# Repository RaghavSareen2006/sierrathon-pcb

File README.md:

# Sierrathon PCB Design – Pocket Lab

KiCad 10 project for the Sierrathon PCB design hackathon.
Pocket Lab: a keyring-sized USB logic analyzer / voltmeter for engineering students.
Specs, BOM and scoring live in `Resources/`.

## Board outline (done)
- Rounded stick, 75 x 27 mm, 3 mm corners. USB-C on BOTH ends:
  J1 (left, silkscreen "PC") goes to the laptop, J2 (right, silkscreen "PROBE") goes to the circuit under test.
- M4 holes sit right behind each USB-C so the screws take plug-in force:
  MH1/MH3 at (13, 6)/(13, 21), MH2/MH4 at (62, 6)/(62, 21). MH4 doubles as the keyring hole.
  Coordinates are mm from the board's top-left (grid origin is set there).
- Blue drawings on `User.Comments` are placement guides only (J1, J2, RP2040 zone, LED zone,
  R20-R25 zone, hole circles). Delete them once parts are placed.

## Probe port J2 (judges approved adding a USB-C) - ON THE BOARD
J2 is the same USB-C part as J1 (Same Sky UJ20-C-H-G-SMT-TR, SeoHan's CUI_UJ20 footprint), at the right
end of the board, rotated 180 deg from J1. Each signal goes through a 1 kOhm series resistor (R20-R25,
same part as R7/R8) placed right behind J2.

| J2 pins | via | Net | RP2040 |
|---|---|---|---|
| A6 + B6 (D+, tied) | R20 | CH0 | GPIO9 (pin 12) |
| A7 + B7 (D-, tied) | R21 | CH1 | GPIO10 (pin 13) |
| A8 (SBU1) | R22 | CH2 | GPIO11 (pin 14) |
| B8 (SBU2) | R23 | CH3 | GPIO12 (pin 15) |
| A5 (CC1) | R24 | A0 | GPIO26 / ADC0 (pin 38) |
| B5 (CC2) | R25 | A1 | GPIO28 / ADC2 (pin 40) |
| GND pins + shell | | GND | |
| VBUS pins | | not connected (a charger/laptop plugged in here can't push 5 V in) | |

CH0-CH3 are 4 consecutive GPIOs (needed for the PIO logic-analyzer). GPIO0-3 / GPIO27 were the first
plan but there is no room to escape 4 vias under those 0.4 mm-pitch pins, so the channels moved to
GPIO9-12 and A1 to GPIO28 (both still analog-capable / consecutive). Drawn on the main sheet (top right)
with local labels; GPIO0-3 and GPIO27 keep their no-connect flags.

## Team rules for working in this repo
- KiCad files don't merge well. **Only one person edits a given file at a time**
  (`.kicad_sch` = schematic, `.kicad_pcb` = board). Say so in the team chat before you start.
- Before you open KiCad: `git pull`. When you're done: save, close KiCad, then commit and push.
- Never commit while the file is open and unsaved.

## Design rules (already set up – don't change without telling the team)
- 4 layers, 62 mil, 1 oz copper, FR-370HR, green mask / white silk (Board Setup > Physical Stackup).
- Constraints page floors are 4 mil clearance / 5 mil track **on purpose**: they must equal the
  90 Ω USB pair geometry (5 mil trace, 4 mil gap). Everything else is held to 6 mil by net
  classes and by `Sierrathon-PCB Design.kicad_dru` (Board Setup > Custom Rules).
- Net classes: `USB_90R` (USB_P/N, USBR_P/N, D_P/D_N – use the diff-pair router, key `6`),
  `Power` (VBUS, +3.3V, +1.1V, GND – 15 mil), `Default` (8 mil).
- Net names in the schematic must match the PDF exactly or nets won't land in the right class.

## Routing (done - DRC: 0 violations, 0 unconnected, schematic parity clean)
- USB (D_P/D_N, USB_P/USB_N, USBR_P/USBR_N) hand-routed and locked: 5 mil traces, 4 mil gap where
  the pair runs in parallel. USBR_N hops under USBR_P on B.Cu (one via pair) because the ESD chip's
  channel order is the reverse of the RP2040's USB_DM/USB_DP pin order.
- `diff_pair_uncoupled` limit is 7 mm (was 3 mm): each pair has to split around U4, R5/R6 and the swap;
  fine for full-speed USB (12 Mb/s).
- Remaining signals auto-routed with Freerouting (F.Cu/B.Cu only); In1.Cu = GND plane, In2.Cu = +3.3V
  plane (layer type "power", 8 mil plane clearance). GND/+3.3V pads drop to the planes through vias;
  RP2040 exposed pad has 6 thermal vias.
- Y1 uses an exact Abracon ABM8 land pattern (Libraries/Sierrathon.pretty, datasheet in Libraries/datasheets).

## Current status (3:05 PM) - SeoHan's schematic and footprints
- Project schematic = SeoHan's `finalschematic.kicad_sch` (only change: internal project name pointed at this project).
- J1, SW1, SW2, SW3, U3, Y1 use SeoHan's footprints (CUI_UJ20-C-H-G-SMT-TR, SON4_PTS526 SM15 SMTR2 LFS_CNK,
  D6R90_CNK, SOIC127P790X216-8N, XTAL_ABM8-272-T3), aligned pad-for-pad to the routed board. Small DFM edits:
  J1 signal-pin mask margin 0.102 -> 0.04 mm (keeps a mask web at 0.85 mm pitch), J1 silk past the board edge
  removed, duplicate "*" silk text on the PTS526 removed, U3 pin-1 silk dot that sat on copper removed.
- Rules: min annular ring 0.127 -> 0.12 mm (J1 pads have a 0.125 mm ring); USB_90R class + a 4 mil in-pair rule
  also cover the auto-named Net-(U1-USB_DP) / Net-(U1-USB_DM) nets.
- DRC --severity-all --schematic-parity: 0 violations, 0 unconnected, 0 footprint errors.
- Known schematic items left as-is for now: USBR_P/USBR_N and Led5 net names, BOM values on J1/MH1-4/SW3/U2,
  most parts have no MPN/Manufacturer fields, ERC warnings from downloaded symbols' pin types.
- My earlier footprints (SW_CK_*, USB_C_Receptacle_SameSky_*, Crystal_SMD_Abracon_ABM8-*) stay in the library, unused.

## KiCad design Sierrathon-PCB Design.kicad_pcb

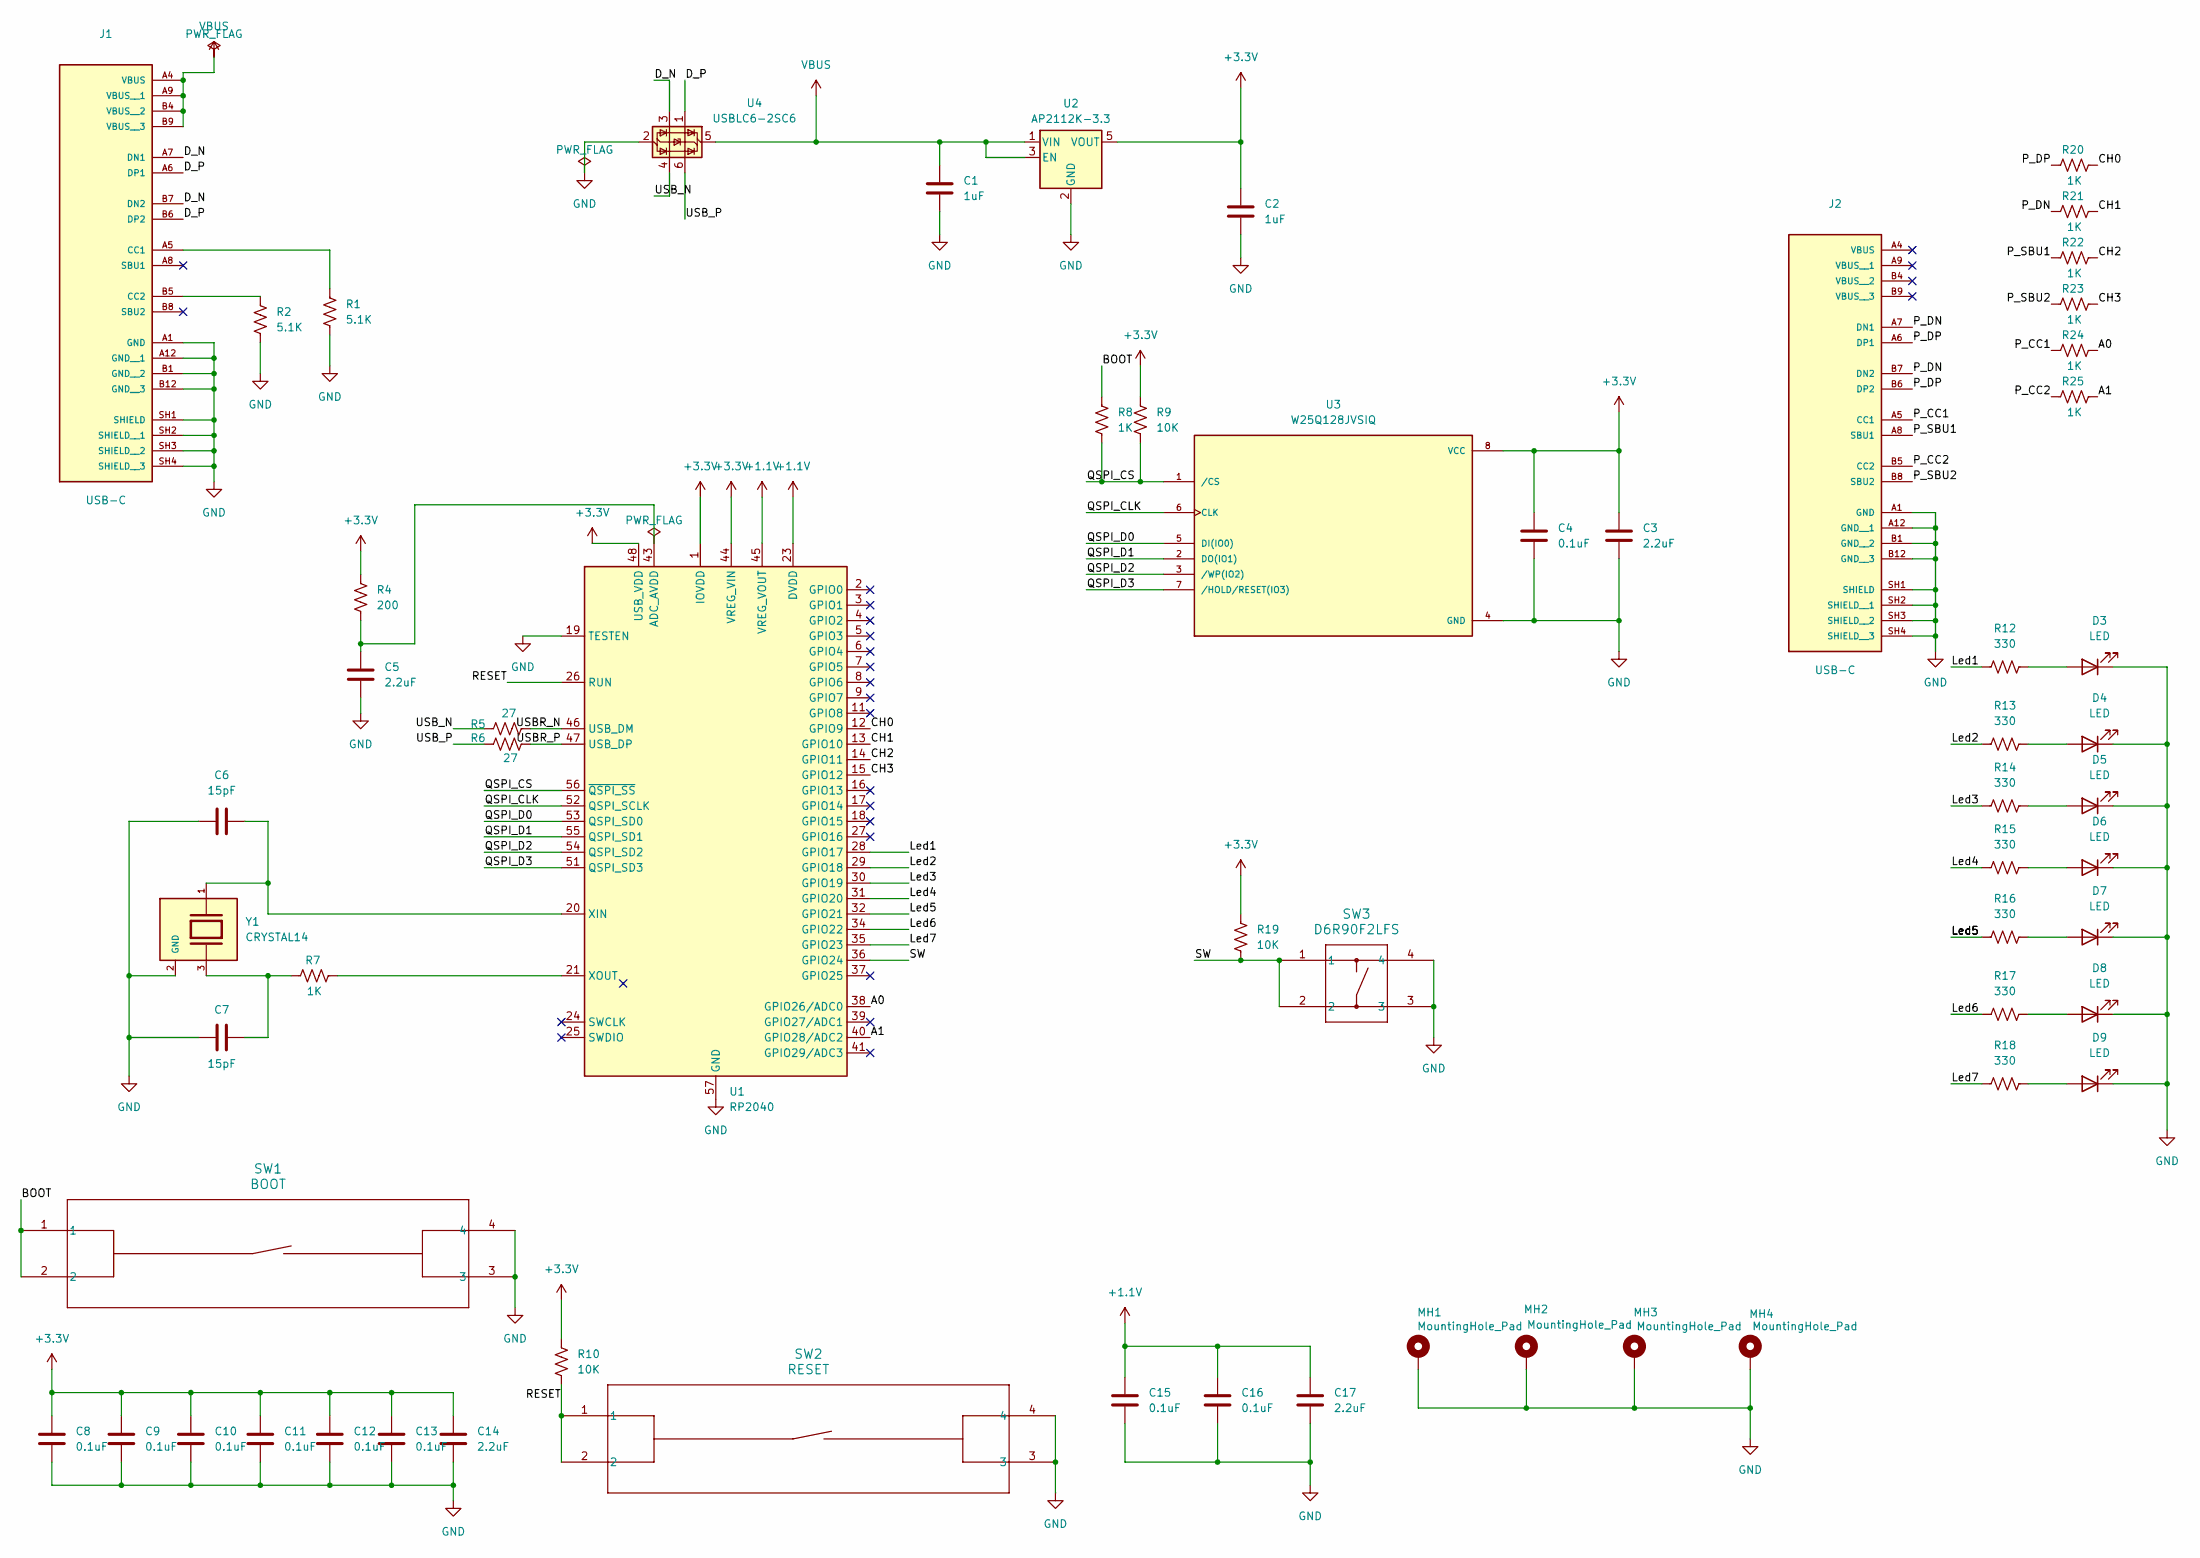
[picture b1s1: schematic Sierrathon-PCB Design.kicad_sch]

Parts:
C1, C2: 1uF; C_0603_1608Metric; MPN GCM188R71C105KA64D
C3, C5, C14, C17: 2.2uF; C_0805_2012Metric; MPN GCM21BR71C225KA64L
C4, C8, C9, C10, C11, C12, C13, C15, C16: 0.1uF; C_0402_1005Metric; MPN GCM155R71C104KA55D
C6, C7: 15pF; C_0402_1005Metric; MPN GCM1555C1H150JA16D
D3, D4, D5, D6, D7, D8, D9: LED; LED_0603_1608Metric; MPN QBLP601-R5
J1, J2: USB-C; CUI_UJ20-C-H-G-SMT-TR; MPN UJ20-C-H-G-SMT-TR
MH1, MH2, MH3, MH4: MountingHole_Pad; MountingHole_4.3mm_M4_Pad
R1, R2: 5.1K; R_0402_1005Metric; MPN RC0402JR-075K1L
R4: 200; R_0603_1608Metric; MPN RC0603JR-07200RL
R5, R6: 27; R_0402_1005Metric; MPN RC0402FR-0727RL
R7, R8, R20, R21, R22, R23, R24, R25: 1K; R_0402_1005Metric; MPN RC0402FR-071KL
R9, R10, R19: 10K; R_0402_1005Metric; MPN RC0402JR-0710KL
R12, R13, R14, R15, R16, R17, R18: 330; R_0402_1005Metric; MPN AF0402JR-07330RL
SW1: BOOT; SON4_PTS526 SM15 SMTR2 LFS_CNK; MPN PTS526SM15SMTR2 LFS
SW2: RESET; SON4_PTS526 SM15 SMTR2 LFS_CNK; MPN PTS526SM15SMTR2 LFS
SW3: D6R90F2LFS; D6R90_CNK; MPN D6R90 F2 LFS
U1: RP2040; QFN-56-1EP_7x7mm_P0.4mm_EP3.2x3.2mm; MPN SC0914(13)
U2: AP2112K-3.3; SOT-23-5; MPN AP2112K-3.3TRG1
U3: W25Q128JVSIQ; SOIC127P790X216-8N; MPN W25Q128JVSIQ TR
U4: USBLC6-2SC6; SOT-23-6; MPN USBLC6-2SC6
Y1: CRYSTAL14; XTAL_ABM8-272-T3; MPN ABM8-272-T3

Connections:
+1.1V: C15.2, C16.2, C17.2, U1.23 (DVDD), U1.45 (VREG_VOUT), U1.50 (DVDD)
+3.3V: C2.1, C3.1, C4.1, C8.2, C9.2, C10.2, C11.2, C12.2, C13.2, C14.2, R4.1, R9.2, R10.2, R19.1, U1.1 (IOVDD), U1.10 (IOVDD), U1.22 (IOVDD), U1.33 (IOVDD), U1.42 (IOVDD), U1.44 (VREG_VIN), U1.48 (USB_VDD), U1.49 (IOVDD), U2.5 (VOUT), U3.8 (VCC)
/A0: R24.2, U1.38 (GPIO26/ADC0)
/A1: R25.2, U1.40 (GPIO28/ADC2)
/BOOT: R8.2, SW1.1, SW1.2
/CH0: R20.2, U1.12 (GPIO9)
/CH1: R21.2, U1.13 (GPIO10)
/CH2: R22.2, U1.14 (GPIO11)
/CH3: R23.2, U1.15 (GPIO12)
/D_N: J1.A7 (DN1), J1.B7 (DN2), U4.3 (I/O2)
/D_P: J1.A6 (DP1), J1.B6 (DP2), U4.1 (I/O1)
/Led1: R12.2, U1.28 (GPIO17)
/Led2: R13.2, U1.29 (GPIO18)
/Led3: R14.2, U1.30 (GPIO19)
/Led4: R15.2, U1.31 (GPIO20)
/Led5: R16.2, U1.32 (GPIO21)
/Led6: R17.2, U1.34 (GPIO22)
/Led7: R18.2, U1.35 (GPIO23)
/P_CC1: J2.A5 (CC1), R24.1
/P_CC2: J2.B5 (CC2), R25.1
/P_DN: J2.A7 (DN1), J2.B7 (DN2), R21.1
/P_DP: J2.A6 (DP1), J2.B6 (DP2), R20.1
/P_SBU1: J2.A8 (SBU1), R22.1
/P_SBU2: J2.B8 (SBU2), R23.1
/QSPI_CLK: U1.52 (QSPI_SCLK), U3.6 (CLK)
/QSPI_CS: R8.1, R9.1, U1.56 (~QSPI_SS), U3.1 (/CS)
/QSPI_D0: U1.53 (QSPI_SD0), U3.5 (DI(IO0))
/QSPI_D1: U1.55 (QSPI_SD1), U3.2 (DO(IO1))
/QSPI_D2: U1.54 (QSPI_SD2), U3.3 (/WP(IO2))
/QSPI_D3: U1.51 (QSPI_SD3), U3.7 (/HOLD/RESET(IO3))
/RESET: R10.1, SW2.1, SW2.2, U1.26 (RUN)
/SW: R19.2, SW3.1, SW3.2, U1.36 (GPIO24)
/USBR_N: R5.2, U1.46 (USB_DM)
/USBR_P: R6.2, U1.47 (USB_DP)
/USB_N: R5.1, U4.4 (I/O2)
/USB_P: R6.1, U4.6 (I/O1)
GND: C1.2, C2.2, C3.2, C4.2, C5.2, C6.1, C7.2, C8.1, C9.1, C10.1, C11.1, C12.1, C13.1, C14.1, C15.1, C16.1, C17.1, D3.1 (K), D4.1 (K), D5.1 (K), D6.1 (K), D7.1 (K), D8.1 (K), D9.1 (K), J1.A1 (GND), J1.A12 (GND__1), J1.B1 (GND__2), J1.B12 (GND__3), J1.SH1 (SHIELD), J1.SH2 (SHIELD__1), J1.SH3 (SHIELD__2), J1.SH4 (SHIELD__3), J2.A1 (GND), J2.A12 (GND__1), J2.B1 (GND__2), J2.B12 (GND__3), J2.SH1 (SHIELD), J2.SH2 (SHIELD__1), J2.SH3 (SHIELD__2), J2.SH4 (SHIELD__3), MH1.1 (1_1), MH2.1 (1_1), MH3.1 (1_1), MH4.1 (1_1), R1.2, R2.2, SW1.3, SW1.4, SW2.3, SW2.4, SW3.3, SW3.4, U1.19 (TESTEN), U1.57 (GND), U2.2 (GND), U3.4 (GND), U4.2 (GND), Y1.2 (GND), Y1.4 (GND)
unnamed: C7.1, R7.1, Y1.3
unnamed: D3.2 (A), R12.1
unnamed: D4.2 (A), R13.1
unnamed: D5.2 (A), R14.1
unnamed: D6.2 (A), R15.1
unnamed: D7.2 (A), R16.1
unnamed: D8.2 (A), R17.1
unnamed: D9.2 (A), R18.1
unnamed: J1.A5 (CC1), R1.1
unnamed: J1.B5 (CC2), R2.1
unnamed: C5.1, R4.2, U1.43 (ADC_AVDD)
unnamed: C6.2, U1.20 (XIN), Y1.1
unnamed: R7.2, U1.21 (XOUT)
VBUS: C1.1, J1.A4 (VBUS), J1.A9 (VBUS__1), J1.B4 (VBUS__2), J1.B9 (VBUS__3), U2.1 (VIN), U2.3 (EN), U4.5 (VBUS)

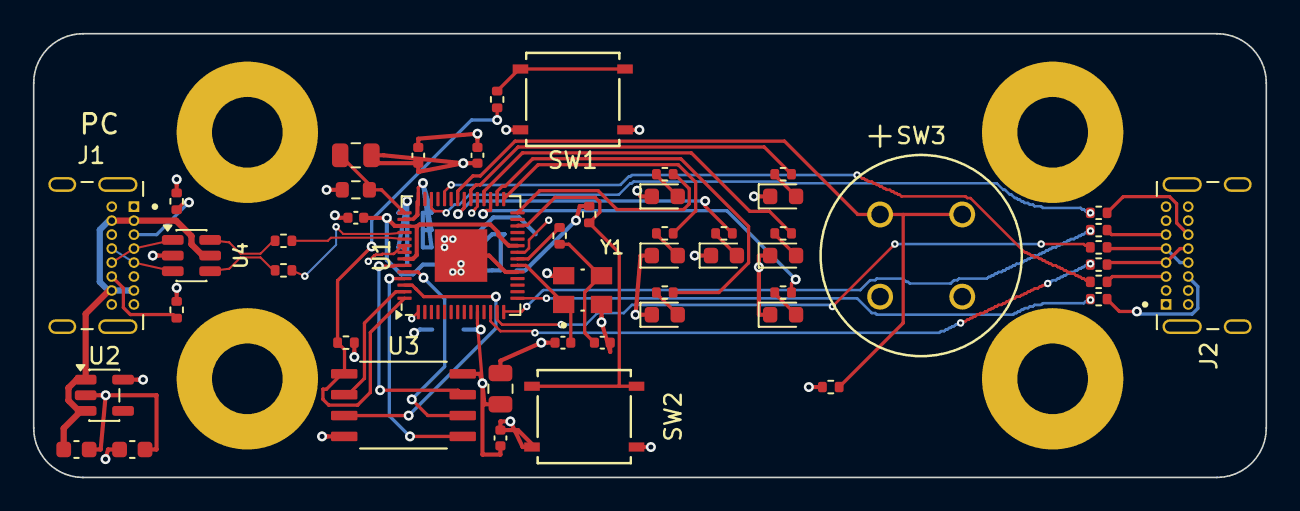
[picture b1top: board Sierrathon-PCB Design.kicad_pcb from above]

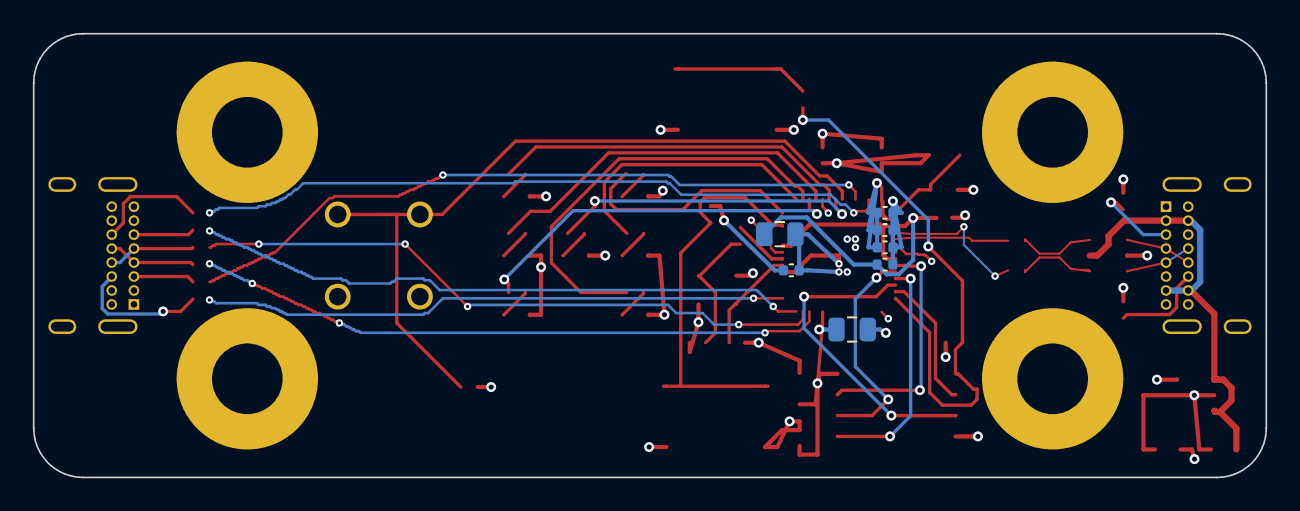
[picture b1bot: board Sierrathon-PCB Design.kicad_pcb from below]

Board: 4 copper layers, 75.0 x 27.0 mm, 61 parts (7 on the bottom side), 51 nets.

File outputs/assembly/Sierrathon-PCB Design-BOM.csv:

"Reference","Value","Footprint","Qty","MPN","Manufacturer","Description","DNP"
"C1,C2","1uF","Capacitor_SMD:C_0603_1608Metric","2","GCM188R71C105KA64D","Murata Electronics","Unpolarized capacitor",""
"C3,C5,C14,C17","2.2uF","Capacitor_SMD:C_0805_2012Metric","4","GCM21BR71C225KA64L","Murata Electronics","Unpolarized capacitor",""
"C4,C8,C9,C10,C11,C12,C13,C15,C16","0.1uF","Capacitor_SMD:C_0402_1005Metric","9","GCM155R71C104KA55D","Murata Electronics","Unpolarized capacitor",""
"C6,C7","15pF","Capacitor_SMD:C_0402_1005Metric","2","GCM1555C1H150JA16D","Murata Electronics","Unpolarized capacitor",""
"D3,D4,D5,D6,D7,D8,D9","LED","LED_SMD:LED_0603_1608Metric","7","QBLP601-R5","QT Brightek (QTB)","Light emitting diode",""
"J1,J2","USB-C","Sierrathon:CUI_UJ20-C-H-G-SMT-TR","2","UJ20-C-H-G-SMT-TR","Same Sky (Formerly CUI Devices)","Type C, USB 2.0, 480 Mbps, 20 Vdc, 5 A, Right Angle, Gold Flash, Surface Mount, Black Insulator, USB Receptacle",""
"R1,R2","5.1K","Resistor_SMD:R_0402_1005Metric","2","RC0402JR-075K1L","YAGEO","Resistor, US symbol",""
"R4","200","Resistor_SMD:R_0603_1608Metric","1","RC0603JR-07200RL","YAGEO","Resistor, US symbol",""
"R5,R6","27","Resistor_SMD:R_0402_1005Metric","2","RC0402FR-0727RL","YAGEO","Resistor, US symbol",""
"R7,R8,R20,R21,R22,R23,R24,R25","1K","Resistor_SMD:R_0402_1005Metric","8","RC0402FR-071KL","YAGEO","Resistor, US symbol",""
"R9,R10,R19","10K","Resistor_SMD:R_0402_1005Metric","3","RC0402JR-0710KL","YAGEO","Resistor, US symbol",""
"R12,R13,R14,R15,R16,R17,R18","330","Resistor_SMD:R_0402_1005Metric","7","AF0402JR-07330RL","YAGEO","Resistor, US symbol",""
"SW1","BOOT","Sierrathon:SON4_PTS526 SM15 SMTR2 LFS_CNK","1","PTS526SM15SMTR2 LFS","C&K","",""
"SW2","RESET","Sierrathon:SON4_PTS526 SM15 SMTR2 LFS_CNK","1","PTS526SM15SMTR2 LFS","C&K","",""
"SW3","D6R90F2LFS","Sierrathon:D6R90_CNK","1","D6R90 F2 LFS","C&K","",""
"U1","RP2040","Package_DFN_QFN:QFN-56-1EP_7x7mm_P0.4mm_EP3.2x3.2mm","1","SC0914(13)","Raspberry Pi","A microcontroller by Raspberry Pi, Dual ARM Cortex-M0+, 133MHz, no flash, 264KB SRAM, 8 PIO state machines, VQFN-56",""
"U2","AP2112K-3.3","Package_TO_SOT_SMD:SOT-23-5","1","AP2112K-3.3TRG1","Diodes Incorporated","600mA low dropout linear regulator, with enable pin, 3.8V-6V input voltage range, 3.3V fixed positive output, SOT-23-5",""
"U3","W25Q128JVSIQ","Sierrathon:SOIC127P790X216-8N","1","W25Q128JVSIQ TR","Winbond Electronics","FLASH - NOR Memory IC 128Mb (16M x 8) SPI - Quad I/O, QPI, DTR 133 MHz 8-SOIC",""
"U4","USBLC6-2SC6","Package_TO_SOT_SMD:SOT-23-6","1","USBLC6-2SC6","STMicroelectronics","Very low capacitance ESD protection diode, 2 data-line, SOT-23-6",""
"Y1","CRYSTAL14","Sierrathon:XTAL_ABM8-272-T3","1","ABM8-272-T3","Abracon LLC","12 MHz ±30ppm Crystal 10pF 50 Ohms 4-SMD, No Lead",""
